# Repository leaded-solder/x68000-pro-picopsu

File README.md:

## Introduction
This is a replacement power supply board for the Sharp X68000 PRO (CZ-652C) desktop computer from 1989. It uses a PicoPSU and an off-board 12VDC power supply to provide the power rails, and handles the unique soft-power-on logic of the X68Ks. It replaces the power supply known as UADP-0070CEZZ.

Note that this board does NOT support the PRO2 model (CZ-653C)! That model uses a completely different power supply layout, identical to the tower machines. See below.

The main benefits of this supply versus the original are:
 - Brand-new board with modern quality control, undamaged by capacitor leakage or wear-and-tear;
 - Optional "Standby" and "Power Good" lights for debugging;
 - Support for 3-wire fans (tachometer is unused) through an optional 3-pin fan header;
 - Depending on the off-board supply used, it supports multiple wall voltages such as Canadian 120V, instead of just Japanese 100V. The Meanwell EPS-65S-12, for instance, claims support for 80 to 264VAC. No step-down converter is necessary.

No trademark infringement is intended, and logos are used for informational purposes only.

## Safety Warning
Please note that this board is produced as a hobbyist project. I am not a professional electrical engineer, and I cannot make any guarantees regarding the electrical safety of this board once installed. If you do find safety issues with the board or its assembly procedure, please let me know immediately.

Additionally, if you are uncomfortable or nervous with building an electrical appliance that plugs into high voltage, please do not attempt the assembly and use of this board.

## Compatibility
Before purchasing anything, including the fabrication of this board, first disassemble your PRO and verify your power supply. It should look like this:

PRO2 models have a different power supply, which looks to be identical to the "Tetris-piece" supply of the tower models. This board will not fit that style of power supply case; [use the mattsoft board instead](https://github.com/mattsoft/X68K_Pico_PSU_v2).

Please note that [the wiring colours are _also_ different for PRO2 models and tower models](https://blog.goo.ne.jp/kawalab_net/e/a0a71a56ef128293a3bc617afcea7ec3).

## Bill of Materials

| Component | Source link          | Comments |
|-----------|----------------------|----------|
| 12V DC power supply (I used a Meanwell EPS-65S-12) | [Digi-Key 1866-1733-ND](https://www.digikey.ca/en/products/detail/mean-well-usa-inc/EPS-65S-12/7703210) | Accepts a 3"x2" or 4"x2" supply |
| PicoPSU   | | I used an 80W model, be aware of the power limit (W) of the 12V supply. |
| A 3-prong electrical cord | [Digi-Key AE10675-ND](https://www.digikey.ca/en/products/detail/assmann-wsw-components/AK500-16-OE-5-1-5/2504516) (1.50m) | I cut up an Apple MagSafe extension cord for mine. |
| A ring terminal for the ground prong of the cord | TODO | Make sure the ring terminal matches the gauge of the earth/ground conductor of the cord. |
| Rubber strain-relief grommet for the power cord (recommended) | [uxcell 27x9x6mm](https://www.amazon.ca/Uxcell-Rubber-Square-Strain-Protector/dp/B016UFGHUK/) | |
| 74LS04 or 74HCT04 (DIP) | [Digi-Key 296-2083-5-ND](https://www.digikey.ca/en/products/detail/texas-instruments/CD74HCT04E/38238) | |
| 2x 7-pin screw terminals (5.00mm) | [Digi-Key 277-1582-ND](https://www.digikey.ca/en/products/detail/phoenix-contact/1935213/568619) | Please use ferrule crimps (see below) |
| 24-pin ATX connector | [Digi-Key WM3811-ND](https://www.digikey.ca/en/products/detail/molex/0039281243/356033) | 20-pin can also be used |
| 3-pin fan header | [Digi-Key WM19538-ND](https://www.digikey.ca/en/products/detail/molex/0038006293/3160035) | 2-pin or a regular 0.1" pin header can also be used |
| 4.7kΩ through-hole resistor | [Digi-Key CF14JT4K70CT-ND](https://www.digikey.ca/en/products/detail/stackpole-electronics-inc/CF14JT4K70/1741428) | Pull-up for soft power logic |
| 0.1µF through-hole capacitor | TODO | |
| 2x 100Ω through-hole resistors (optional) | TODO | Current limiters for troubleshooting LEDs |
| 2x through-hole green LEDs (optional) | TODO | For troubleshooting LEDs |
| 4-pin JST VH "VHR-4N" female connector | [Digi-Key 455-1185-ND](https://www.digikey.ca/en/products/detail/jst-sales-america-inc/VHR-4N/608626) | For connecting the PicoPSU to the Meanwell (see below for notes on tools.) Some eBay sellers offer a pre-crimped harness using this connector, but I have not seen any for electrical cords |
| 3-pin JST VH "VHR-3N" female connector | [Digi-Key 455-1184-ND](https://www.digikey.ca/en/products/detail/jst-sales-america-inc/VHR-3N/608625) | For connecting the wall cord to the Meanwell. |
| JST SVH-21T-P1.1 crimp terminals | [Digi-Key 455-1133-1-ND](https://www.digikey.ca/en/products/detail/jst-sales-america-inc/SVH-21T-P1-1/527368) | For building the PicoPSU-to-Meanwell connector and wall-to-Meanwell connector |
| Vinyl spacers | TODO | For lifting the Meanwell board off the PCB | 
| M3 screws with nuts | TODO | For fastening the Meanwell board through the vinyl spacers |
| Replacement cooling fan (optional) | [Noctua NF-A6x25](https://noctua.at/en/nf-a6x25-pwm) | Can reuse original fan if desired, but mine was gross. |

## Tools
### JST VH crimper
You will likely want a JST VH-specific crimper to crimp the pins for the wiring connection from the PicoPSU to the Meanwell 12V supply. I tried a few times with various universal crimpers and had no luck.

The crimper I successfully used was called [SNA-02BM](https://www.aliexpress.com/item/4000246209070.html) on AliExpress, but be careful as their "all in one" crimper jaw kit does _not_ include the JST VH jaws.

Another budget-priced option is the [Engineer PA-21](https://www.nejisaurus.engineer.jp/product-page/pa-21-%E7%B2%BE%E5%AF%86%E5%9C%A7%E7%9D%80%E3%83%9A%E3%83%B3%E3%83%81-1).

If you are in a hurry, you can always desolder the wiring harness from the PicoPSU and the connectors from the Meanwell, and then directly solder wires between these two units to pass the +12V to the PicoPSU. Whenever you are removing the wires from the PicoPSU, be careful to keep track of which pin is which on the PicoPSU, as the polarity was not marked on my PicoPSU otherwise.

You will probably still have to crimp the electrical cord, as many electrical standards bodies frown upon soldering it.

### Ferrule crimper
It is strongly recommended to crimp the computer's wiring harness with ferrules before inserting them into the screw terminals. Doing so will [improve the reliability of a high-current connection](https://www.youtube.com/watch?v=bJk0mzaATI4&ab_channel=efixx), and also reduce the risk of shorting between pins if wire strands splay out while tightening the screw terminals. Ferrule crimpers, complete with ferrule kits, are inexpensive on most online marketplaces – I used the generic red-and-blue one which is sold under dozens of names.

### High-quality JIS screwdriver
Disassembly of the system will go much better if you have a [JIS screwdriver](https://rtstools.com/jis-vs-phillips-screwdrivers-and-where-to-buy-a-jis-screwdriver/) on hand. JIS is commonly used in Japanese computers, vehicles, and machines, and if you keep camming out and ruining screws, that's probably because you are using a Phillips screwdriver to turn them. JIS screws can be recognized by their cross head and identifying dot. My favourite brand of JIS screwdriver is [Vessel](https://www.vesseltoolsusa.com/product/screwdriver), but Hozan also makes a good driver.

### The Essentials
In general, you should also have the following tools on hand:
 * A crimper capable of crimping ring terminals (pliers work in a pinch;)
 * Wire strippers;
 * A heat gun if you are using heat-shrink ring terminals (recommended;)
 * Temperature-controlled soldering iron with appropriate electronics solder (I recommend Kester 63/37)

## Assembly Process
Please do not attempt the manufacture of this board if you are unsure or nervous about it.

### 1. Disassembly of Old Power Supply
Once the power supply unit is removed from the computer, unscrew the screws on the outside of the power supply. Keep track of where each one came from.

Once the old power supply board is exposed, cut the wiring harness as close to the board as possible so that you have lots of wire length to work with. If your old power board is extremely corroded (it probably is) you should check the wiring. Any "greening up" or general crunchiness of the original wire means that it's safer and more reliable for it to be thrown away and replaced with new, stranded, copper wire.

Make sure you preserve the grommet for the original harness, as it helps protect the wiring from the sharp edges of the power supply case.

Unscrew the original supply board and set it aside, just in case. At this point, you may also want to chuck the old fan in the trash and order a Noctua.

The case itself can be cleaned using dish soap and a firm brush. I used a dishwasher for mine, but it didn't do as good of a job without heavy scrubbing.

### 2. Soldering the new PCB
This is the most straightforward part. Move in order from the lowest-height to the tallest components. Depending on how much of your original harness is left, it may help to point the opening of the screw terminals both "southward" towards the opening.

Make sure the 74LS04 is installed the correct way around before soldering. The notch on the IC (and on the socket, if you're using one) should match the notch on the PCB's silkscreen.

When installing through-hole LEDs, there is a flat side and a rounded side. The flat side should be pointing towards the _negative_ terminal of the LED footprint. It is optional to install the LEDs, and if you don't, there's no need to install the R1 and R2 current-limiting resistors for those LEDs.

If you only have a 20-pin ATX connector instead of a 24-pin ATX connector, follow the legend on the PCB to know which pins to install it into. The unused four plated holes can be ignored as the PicoPSU will not conceivably make contact with them. Note that this configuration has not been tested.

### 3. 12V converter to PicoPSU harness
The PicoPSU is shipped with a DC barrel plug on the end of two wires that are soldered into the top of the PicoPSU unit. Chop off the barrel plug, strip the wiring back, and crimp it for the 12V converter you are using. Pay attention to the pinout of the converter and of the PicoPSU!

When you are done, the PicoPSU and the 12V converter should be connected. It is also possible to solder the PicoPSU directly to the converter, but it makes it kind of a pain to take apart later.

### 4. Wall power to 12V converter harness
If at any point in this step you find yourself unsure, confused, or nervous, immediately stop and consult an electrician.

Find a suitable donor 3-prong power cord, and cut the end off of it. Strip back the insulation to expose the three wires which a power cord consists of.

In North America, these three wires are black (live), white (neutral), and green (earth/ground.) If that's not the case on the cord you just cut open, or if you live outside North America, please consult a local electrician for reference on what is safe to do.

At this point, you should slip the grommet you're going to use over the cord, _before_ you install the crimp connector. Don't forget and wait until later, you will regret it.

It is strongly recommended that you now tie [an underwriter's knot](https://www.thespruce.com/what-is-an-underwriters-knot-1152873). This knot adds strain relief, but it is essential for safety so that passing children and YouTubers can't pull a live electrical cord out of the back of the computer.

Paying attention to the footprint for your 12V converter, crimp the live and neutral wires for the converter, and crimp a ring terminal onto the ground. On the double-insulated converter which I used, no ground lug is exposed, so the ring terminal had to be bolted directly to the case of the supply.

Unlike the PicoPSU connection, in North America, it is generally frowned upon (and is usually against local electrical code) to solder the live and neutral conductors directly to anything. A soldered connection is considered less reliable and consistent.

Once this step is complete, you should be able to plug a wall cord into the 12V converter, which is itself plugged into the PicoPSU. Don't plug the electrical cord into the wall yet.

### 5. Installing the 12V converter
Using the spacers and fastening nuts, install the 12V converter into the board. It should be spaced far enough away that any components on the underside of the board can not conceivably make contact with the board. You might also want to consult the datasheet for your converter to see if there are any special requirements with airflow, etc.

Once this step is complete, the converter should be rigidly attached to the board. You're almost done!

### 6. Fan installation
If you removed the fan in a previous step (e.g. replacing it with a Noctua) you should now bolt the new fan in. It isn't _impossible_ to do it with the board installed, but it's much more of a pain.

Make sure to screw it down with the same screws you originally used, and route the harness into the fan connector. If you are using a 2-pin fan (such as the original) it should be connected across the GND and 12V pins.

### 7. Board installation
Drop the board into the vacated power supply case, and screw it down using the supplied holes. You'll want to do a quick check here to make sure that your converter screws are not even remotely close to contacting the metal of the case.

Slot the PicoPSU into the ATX connector, and connect it to the 12V converter.

### 8. Installing the wall cord
Install the power cord into the back of the shell. The "slot" in the rubber grommet should slide smoothly but firmly into the hole on the supply shell, and stay there.

Make sure the green "ground" wire of the wall cord has continuity with the metal case. Make sure the crimps on the live/neutral connector are tight, and that they make good contact with the pins of the 12V converter.

You should now be able to test the standby system. Keeping your hands free of the internals of the power supply, plug the cord into the wall. The "standby" LED, if installed, should illuminate.

Congratulations: the power is getting from the wall, to the 12V converter, into the PicoPSU and being turned into always-on 5V.

Make sure you unplug the power supply before you move on.

### 9. Building and Routing the Main Harness
Strip back each of the conductors on the original harness. Again, look for "greened up" wires, or especially brittle ones. You can then crimp them with ferrule crimps and install them into the screw terminals.

If you removed the harness grommet, now is the time to reinstall it. It gets a lot harder to do after this.

Here is the colour guide for _my_ machine: yours may be different, and if it is please let me know so I can update this. It followed the pattern shown on [the NFGGames power-supply rebuild page](https://nfggames.com/nfg/x68repair/).

| Colour | Voltage | Comment |
|--------|---------|---------|
| Orange | +5V standby | Connect to +5VSB pad |
| Red    | +5V     | |
| Blue   | -12V    | |
| Black  | Ground  | |
| Yellow | +12V    | |
| Brown  | PwrOn   | Connect to "PwrOn" pad |

At this point, you may also want to substitute one of the original floppy power cables for an additional 4-pin Molex or Berg power cable, which will make powering a hard drive or SCSI2SD easier in the future.

If you are colour-blind, ask someone who isn't to help you identify the wires. The embarrassment of getting roasted on your local Discord server is a lot cheaper than buying a new motherboard.

You should now be able to plug in the supply. Without the rest of the X68000 attached, the supply will turn on as soon as power is applied. The "Power Good" light should illuminate, and you should see appropriate voltages on all of the connectors. If installed, your fan should be running.

### 10. Final Assembly

Here are all the little steps:

 1. Put the top back on the case, and screw it down. Pay special attention to make sure it isn't pinching or otherwise cutting into any of the nest of wires running around inside the case.
 2. Ensure that the fan, likewise, is not able to hit any wires including its own harness. You might have to ziptie wires back. Remember also that retro computers tend to get picked up and moved a lot, so make sure that the wires aren't just "out of the way for now."
 3. Reinstall the power supply to the computer. Make sure that it is rigidly held by the sides of the case and the crossbars.
 4. Reattach the power harness to the motherboard and all devices. You might find it easier to reach the floppies, especially, if you do this _before_ the power supply is bolted down into the computer.
 5. Screw down the power supply onto the crossbars, locking it in place.
 6. Do a final sanity check to make sure you didn't miss any connectors or have anything pinched or shorted.

### 11. It's Showtime
Connect the 3-prong power cord to the wall outlet. The computer's "standby" light should now come on. You might be able to see the "standby" light on the PSU PCB itself, if you can stare through the fan.

Push the power button on the front of the computer. The power supply should now start, signalled by the fan revving up, and you should (hopefully) see a running computer.

Congratulations, you have successfully kept the scene alive!

## Version History
 * v0.4: Fix 4" footprint, add protection resistor to power-on signal
 * v0.3: Move pull-up to input side of 74LS04, so that soft power on works.
 * v0.2: Fix AC/DC converter holes. Fix unused 74LS04 gates. Move ATX connector for more "hand room" around it. Remove thermal reliefs for power pours.
 * v0.1: Initial version. AC/DC converter footprint holes did not line up.

## License
In keeping with the license of the original mattsoft board, this derivation is also GNU GPL 3.0. Please see the LICENSE file for more details.

## Credits
Thanks to [mattsoft from the nfggames forum](https://nfggames.com/forum2/index.php?topic=6510.0) for the original idea and implementation for the "Tetris-piece" X68000 OG/ACE power supply, including much of the BOM for this one.

Thanks to [Tim Maxwell's ATX Breakout project](http://timmaxwell.org/pages/atx-breakout/) for contributing the symbol for the ATX connector.

Thanks to Dave Park for advice on thermal reliefs and reliable usage of the 74LS04.

Thanks to Kanji for test-building one of these and taking good pictures for the assembly instructions.

Thanks to sampson for finding a mistake in the testing instructions.

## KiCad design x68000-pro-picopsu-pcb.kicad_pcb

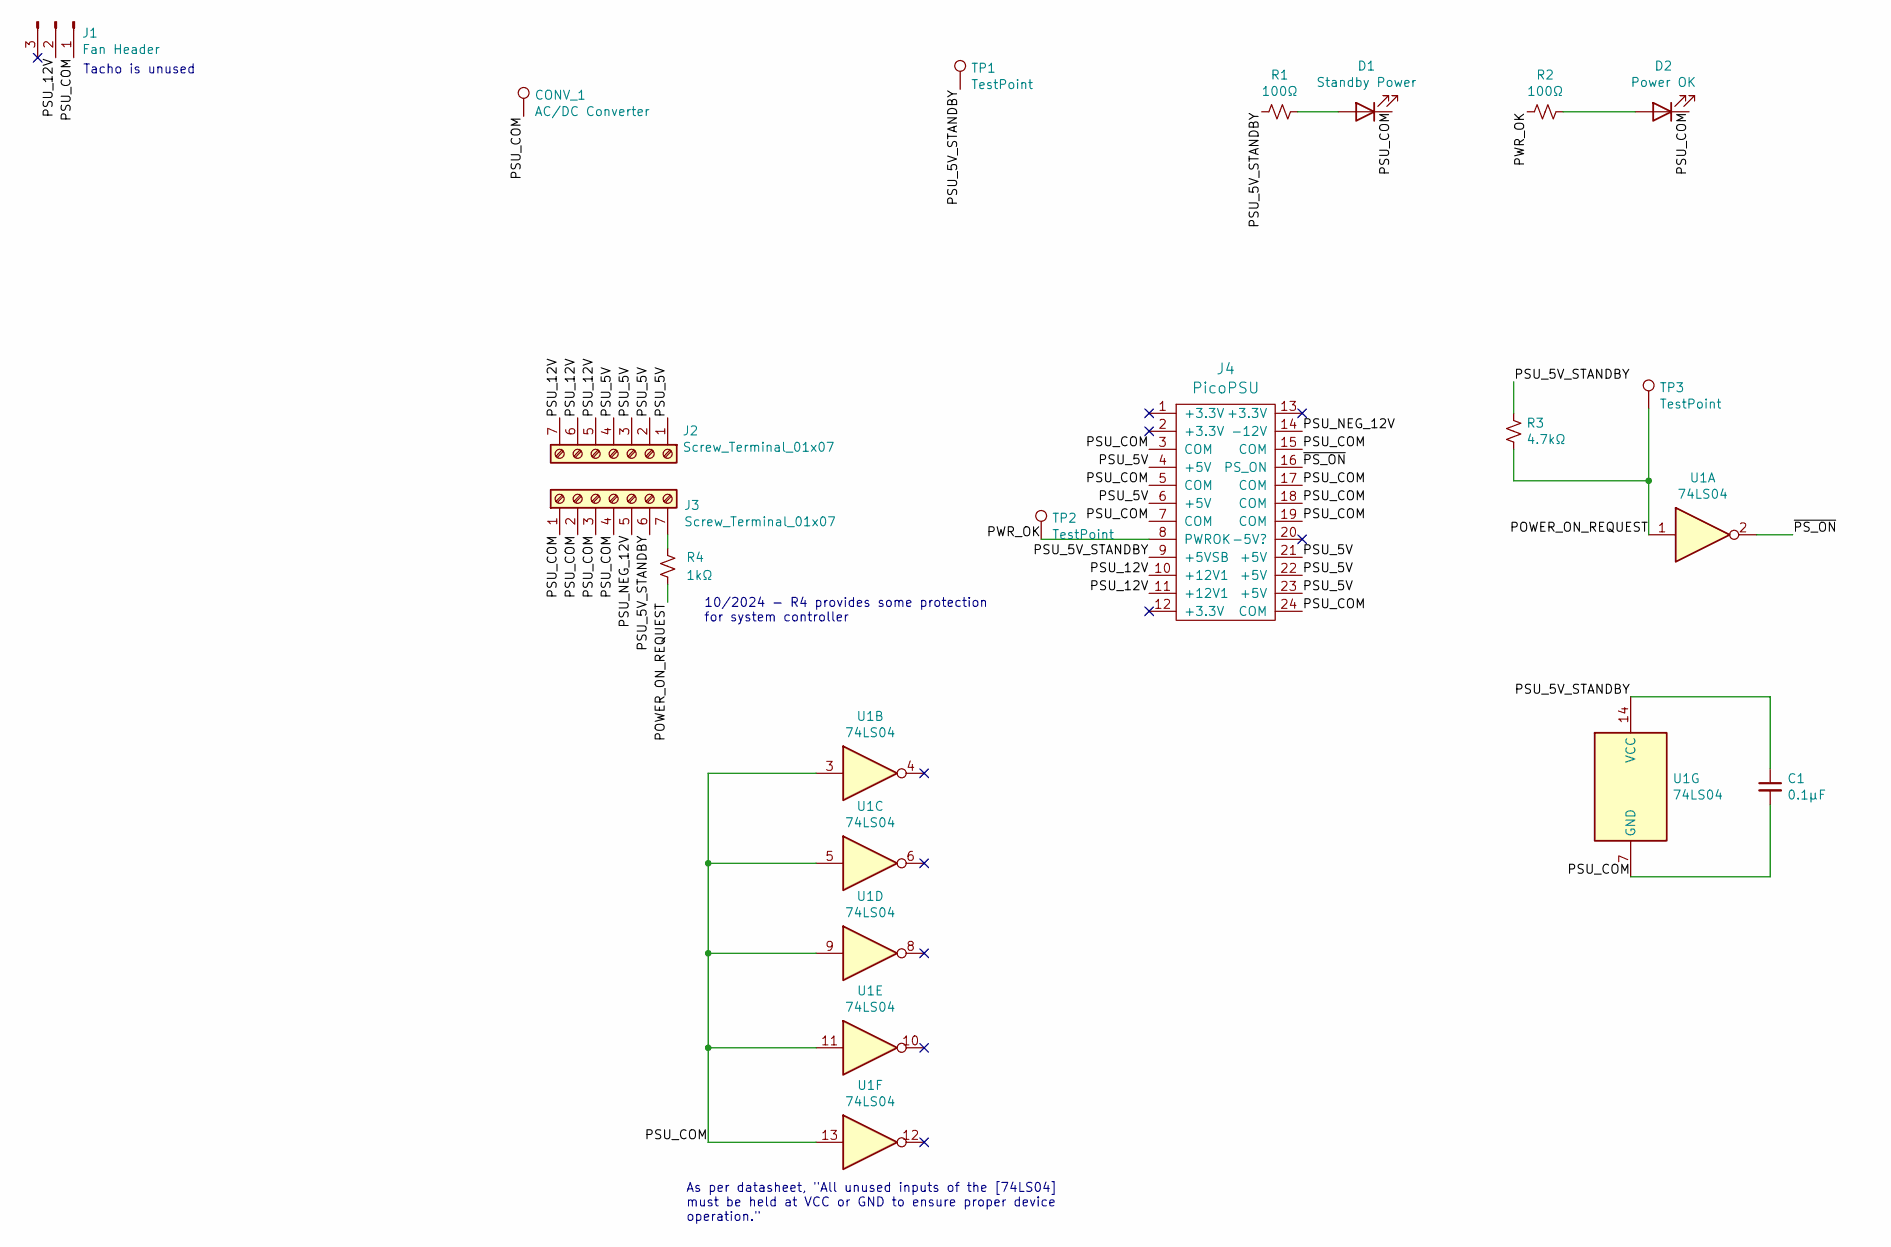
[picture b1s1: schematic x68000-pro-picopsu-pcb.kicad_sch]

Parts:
C1: 0.1µF; C_Disc_D3.0mm_W2.0mm_P2.50mm
CONV_1: AC/DC Converter; 3x2_4x2
D1: Standby Power; LED_D3.0mm
D2: Power OK; LED_D3.0mm
J1: Fan Header; Molex_KK-254_AE-6410-03A_1x03_P2.54mm_Vertical; DigiKey WM19538-ND
J2, J3: Screw_Terminal_01x07; TerminalBlock_Phoenix_PT-1,5-7-5.0-H_1x07_P5.00mm_Horizontal
J4: PicoPSU; Molex_Mini-Fit_Jr_5566-24A_2x12_P4.20mm_Vertical
R1, R2: 100Ω; R_Axial_DIN0207_L6.3mm_D2.5mm_P10.16mm_Horizontal
R3: 4.7kΩ; R_Axial_DIN0207_L6.3mm_D2.5mm_P10.16mm_Horizontal
R4: 1kΩ; R_Axial_DIN0207_L6.3mm_D2.5mm_P10.16mm_Horizontal
TP1, TP2, TP3: TestPoint; TestPoint_Plated_Hole_D2.0mm
U1: 74LS04; DIP-14_W7.62mm_Socket_LongPads

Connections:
/POWER_ON_REQUEST: R3.2, R4.2, TP3.1, U1.1
/PSU_5V: J2.1, J2.2, J2.3, J2.4, J4.4 (+5V), J4.6 (+5V), J4.21 (+5V), J4.22 (+5V), J4.23 (+5V)
/PSU_5V_STANDBY: C1.1, J3.6, J4.9 (+5VSB), R1.2, R3.1, TP1.1, U1.14 (VCC)
/PSU_12V: J1.2, J2.5, J2.6, J2.7, J4.10 (+12V1), J4.11 (+12V1)
/PSU_COM: C1.2, CONV_1.1, D1.1 (K), D2.1 (K), J1.1, J3.1, J3.2, J3.3, J3.4, J4.3 (COM), J4.5 (COM), J4.7 (COM), J4.15 (COM), J4.17 (COM), J4.18 (COM), J4.19 (COM), J4.24 (COM), U1.3, U1.5, U1.7 (GND), U1.9, U1.11, U1.13
/PSU_NEG_12V: J3.5, J4.14 (-12V)
/PWR_OK: J4.8 (PWROK), R2.1, TP2.1
/~PS_ON: J4.16 (PS_ON), U1.2
unnamed: D1.2 (A), R1.1
unnamed: D2.2 (A), R2.2
unnamed: J3.7, R4.1

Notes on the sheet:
As per datasheet, "All unused inputs of the [74LS04] must be held at VCC or GND to ensure proper device operation."
Tacho is unused
10/2024 - R4 provides some protection for system controller

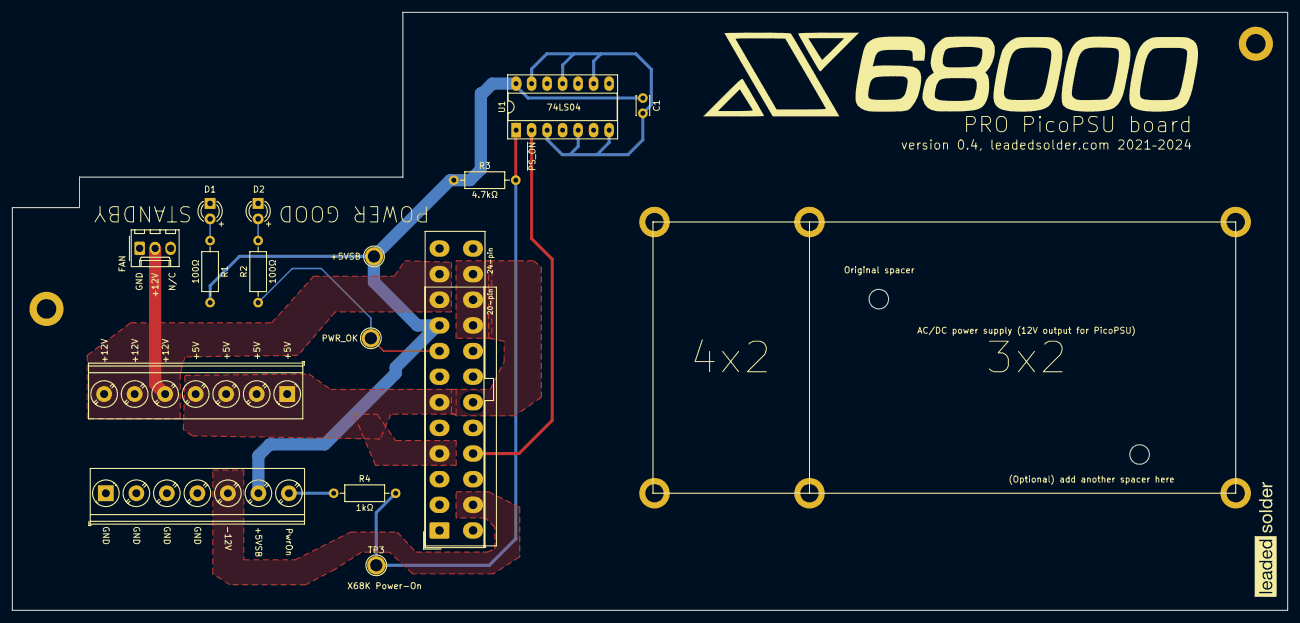
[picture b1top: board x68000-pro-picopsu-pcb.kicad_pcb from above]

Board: 2 copper layers, 209.0 x 98.0 mm, 16 parts (0 on the bottom side), 11 nets.

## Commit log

2021-06-19 Basic layout
2021-06-19 resistors
2021-06-19 Power pins all connected
2021-06-19 A terrible basic implementation, time to test fit
2021-06-19 Add datasheet
2021-06-19 Zones instead of thin traces
2021-06-19 Giant obnoxious logos
2021-06-19 Everything except central mounting hole
2021-06-19 Central mounting/support hole, in m3
2021-06-19 Small fiddling
2021-06-19 Bonus mounting hole
2021-06-19 Clean up some pad confusion
2021-06-19 Rust logo
2021-06-19 Refill
2021-07-15 Fan header digikey link
2021-07-15 Moved PicoPSU north, no thermal reliefs for ATX
2021-07-15 Tie unused 74ls04 inputs to ground
2021-07-15 mounting holes fixed
2021-07-15 Tweak converter a bit backward, in case they use a 4x2
2021-07-15 Re-plot
2021-07-15 Move fan hed up a bit to make more room for wires
2021-07-15 Track cleanup
2021-07-15 Credits
2021-07-24 Routing fixes (thanks taqueso)
2021-07-31 Mark for LED
2021-08-06 README
2021-08-20 Fix screwup: move 4.7k pullup to input side of inverter
2021-12-20 Working on the BOM
2021-12-30 Direct soldering advice
2022-02-01 V0.3 + assembly instructions
2022-02-01 More DigiKey pns
2022-02-01 Uxcell
2022-02-01 Noctua
2022-02-01 VHR-3N
2022-02-02 Power cord link
2022-02-05 PRO2 warning
2022-02-25 Create LICENSE
2022-02-25 Mention license in README
2022-09-25 Kanji's photos
2022-09-26 Screw terminal pin pitch
2023-06-25 Add PSU part number
2024-05-22 Update README.md
    Use longer cord
2024-10-02 Engineer crimper link
2024-10-24 Add protection resistor to power-on signal to protect syscon just in case
2024-11-12 Fixed 4x2 footprint
2024-11-12 Release notes
2026-04-25 Test fix

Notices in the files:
README.md:
In keeping with the license of the original mattsoft board, this derivation is also GNU GPL 3.0. Please see the LICENSE file for more details.
